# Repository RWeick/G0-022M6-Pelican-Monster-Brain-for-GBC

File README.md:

# G0-022M6-Pelican-Monster-Brain-for-GBC
The schematics, PCB, and flash dumps of three versions of the GBC Pelican Monster Brain.

Version 1.1 is for Pokemon Red and Blue, and comes in a case with a blue BrainBoy sticker/logo.
Version 2.0 is for Pokemon Gold and Silver, and comes in a case with a gold BrainBoy sticker/logo.
Version 3.6 is for every Gameboy Pokemon edition, and comes in a case with a purple Monster Brain sticker/logo.

All components labeled "Unknown" in the schematic were not present on the commercial PCB. This PCB is used for both the Monster Brain and the Codebreaker, and the missing components are present when this board is used in a Codebreaker.

The CPLD is the same between all devices.

The Colorizer button PCB wires solder to the inner two pads of the 4 at the rear top edge of the PCB.

Jumper configuration for normal operation: 

- J1: Pads 2 and 3 are shorted.
- J2: Open.
- J3: Shorted.
- J4: Shorted.

The CPLD functions I've been able to deduce are as follows:

A read must be performed at address 0x100 in order to enable address banking in the CPLD.

The write address to change banks is 0xA000.

The full rom is available from 0x2000 to 0x3FFF by switching either 32 or 64 banks depending on the device. The blue label Brainboy has 64 banks, and the rest of the devices use 32 banks due to smaller eeproms. The maximum known EEPROM size included with an off the shelf device is 512 KB.

PCB Thickness: 0.8 mm

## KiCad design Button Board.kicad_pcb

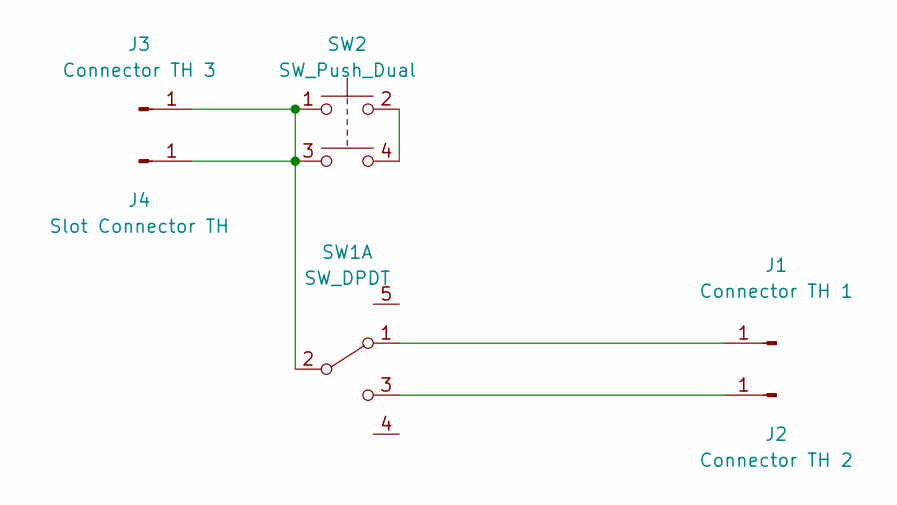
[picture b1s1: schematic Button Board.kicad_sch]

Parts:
J1: Connector TH 1; Connector Hole
J2: Connector TH 2; Connector Hole
J3: Connector TH 3; Connector Hole
J4: Slot Connector TH; Square Slot
SW1: SW_DPDT; Sliding Switch
SW2: SW_Push_Dual; Push Button

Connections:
unnamed: J1.1, SW1.1 (A)
unnamed: J2.1, SW1.3 (C)
unnamed: J3.1, J4.1, SW1.2 (B), SW2.1, SW2.3
unnamed: SW2.2, SW2.4

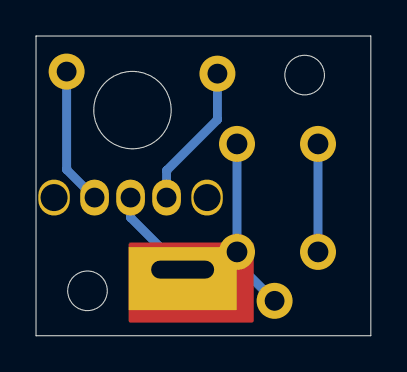
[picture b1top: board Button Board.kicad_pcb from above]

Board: 2 copper layers, 18.6 x 16.6 mm, 9 parts (0 on the bottom side), 4 nets.

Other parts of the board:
H1, H3: MountingHole_2.2mm_M2
H2: MountingHole_4.3mm_M4

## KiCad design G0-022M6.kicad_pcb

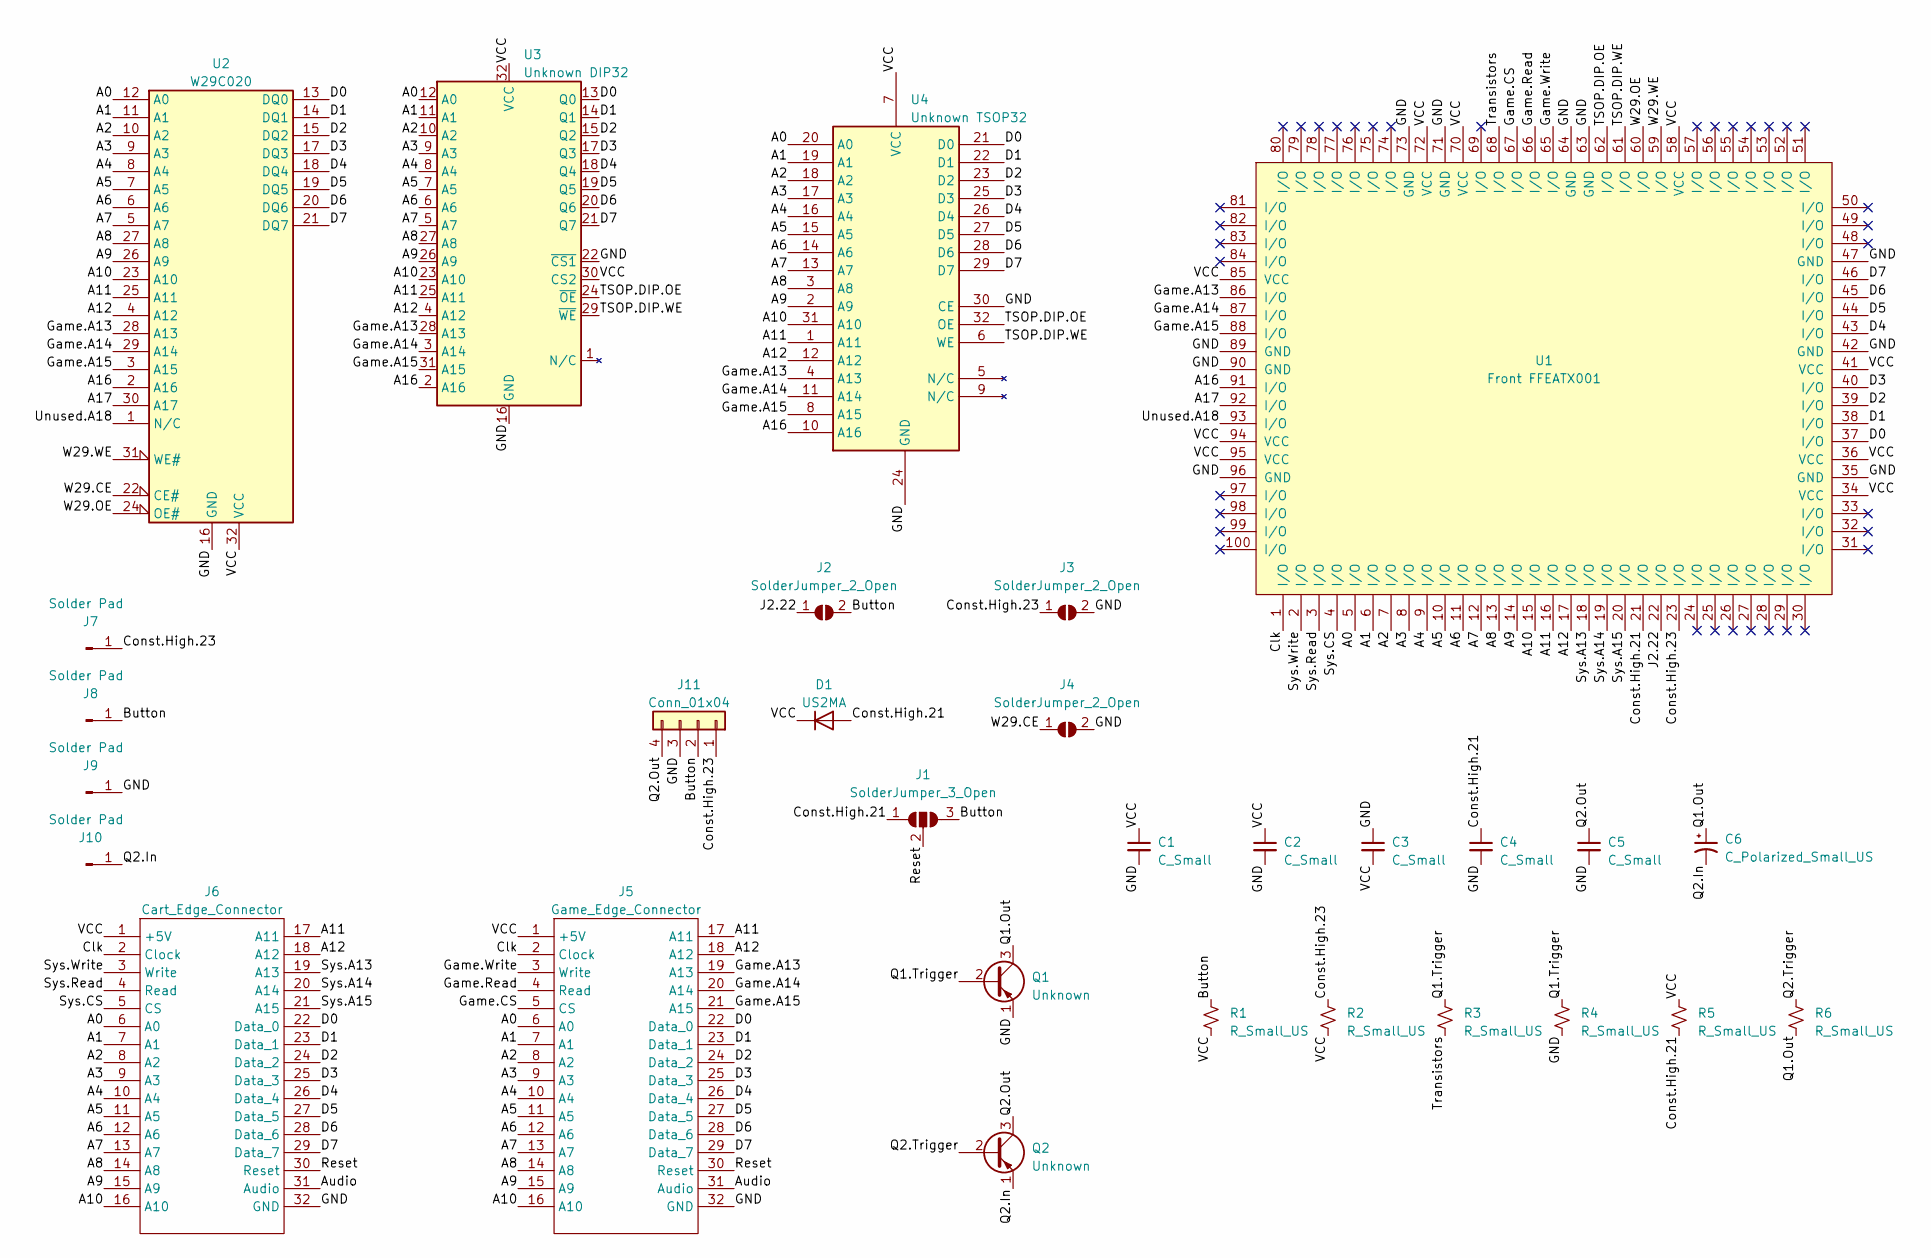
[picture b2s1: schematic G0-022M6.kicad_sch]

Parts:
C1, C2, C3, C4, C5: C_Small; SMD Cap
C6: C_Polarized_Small_US; TH Cap
D1: US2MA; Diode
J1: SolderJumper_3_Open; 3 Pad Jumper
J2, J3, J4: SolderJumper_2_Open; 2 Pad Jumper
J5: Game_Edge_Connector; Cartridge Slot, GBC
J6: Cart_Edge_Connector; ACTUAL GAMEBOY EDGE CONNECTOR
J7, J8, J9, J10: Solder Pad; Rear Circle Pad
J11: Conn_01x04; Rear Edge
Q1, Q2: Unknown; TO-92_Inline
R1, R2, R3, R4, R5, R6: R_Small_US; SMD Res
U1: Front FFEATX001; FFEATX001
U2: W29C020
U3: Unknown DIP32; Unknown Dip
U4: Unknown TSOP32; Unknown TSOP

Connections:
/A0: J5.6 (A0), J6.6 (A0), U1.5 (I/O), U2.12 (A0), U3.12 (A0), U4.20 (A0)
/A1: J5.7 (A1), J6.7 (A1), U1.6 (I/O), U2.11 (A1), U3.11 (A1), U4.19 (A1)
/A2: J5.8 (A2), J6.8 (A2), U1.7 (I/O), U2.10 (A2), U3.10 (A2), U4.18 (A2)
/A3: J5.9 (A3), J6.9 (A3), U1.8 (I/O), U2.9 (A3), U3.9 (A3), U4.17 (A3)
/A4: J5.10 (A4), J6.10 (A4), U1.9 (I/O), U2.8 (A4), U3.8 (A4), U4.16 (A4)
/A5: J5.11 (A5), J6.11 (A5), U1.10 (I/O), U2.7 (A5), U3.7 (A5), U4.15 (A5)
/A6: J5.12 (A6), J6.12 (A6), U1.11 (I/O), U2.6 (A6), U3.6 (A6), U4.14 (A6)
/A7: J5.13 (A7), J6.13 (A7), U1.12 (I/O), U2.5 (A7), U3.5 (A7), U4.13 (A7)
/A8: J5.14 (A8), J6.14 (A8), U1.13 (I/O), U2.27 (A8), U3.27 (A8), U4.3 (A8)
/A9: J5.15 (A9), J6.15 (A9), U1.14 (I/O), U2.26 (A9), U3.26 (A9), U4.2 (A9)
/A10: J5.16 (A10), J6.16 (A10), U1.15 (I/O), U2.23 (A10), U3.23 (A10), U4.31 (A10)
/A11: J5.17 (A11), J6.17 (A11), U1.16 (I/O), U2.25 (A11), U3.25 (A11), U4.1 (A11)
/A12: J5.18 (A12), J6.18 (A12), U1.17 (I/O), U2.4 (A12), U3.4 (A12), U4.12 (A12)
/A16: U1.91 (I/O), U2.2 (A16), U3.2 (A16), U4.10 (A16)
/A17: U1.92 (I/O), U2.30 (A17)
/Audio: J5.31 (Audio), J6.31 (Audio)
/Button: J1.3 (B), J2.2 (B), J8.1, J11.2, R1.1
/Clk: J5.2 (Clock), J6.2 (Clock), U1.1 (I/O)
/Const.High.21: C4.1, D1.2 (A), J1.1 (A), R5.2, U1.21 (I/O)
/Const.High.23: J3.1 (A), J7.1, J11.1, R2.1, U1.23 (I/O)
/D0: J5.22 (Data_0), J6.22 (Data_0), U1.37 (I/O), U2.13 (DQ0), U3.13 (Q0), U4.21 (D0)
/D1: J5.23 (Data_1), J6.23 (Data_1), U1.38 (I/O), U2.14 (DQ1), U3.14 (Q1), U4.22 (D1)
/D2: J5.24 (Data_2), J6.24 (Data_2), U1.39 (I/O), U2.15 (DQ2), U3.15 (Q2), U4.23 (D2)
/D3: J5.25 (Data_3), J6.25 (Data_3), U1.40 (I/O), U2.17 (DQ3), U3.17 (Q3), U4.25 (D3)
/D4: J5.26 (Data_4), J6.26 (Data_4), U1.43 (I/O), U2.18 (DQ4), U3.18 (Q4), U4.26 (D4)
/D5: J5.27 (Data_5), J6.27 (Data_5), U1.44 (I/O), U2.19 (DQ5), U3.19 (Q5), U4.27 (D5)
/D6: J5.28 (Data_6), J6.28 (Data_6), U1.45 (I/O), U2.20 (DQ6), U3.20 (Q6), U4.28 (D6)
/D7: J5.29 (Data_7), J6.29 (Data_7), U1.46 (I/O), U2.21 (DQ7), U3.21 (Q7), U4.29 (D7)
/GND: C1.2, C2.2, C3.1, C4.2, C5.2, J3.2 (B), J4.2 (B), J5.32 (GND), J6.32 (GND), J9.1, J11.3, Q1.1 (E), R4.2, U1.35 (GND), U1.42 (GND), U1.47 (GND), U1.63 (GND), U1.64 (GND), U1.71 (GND), U1.73 (GND), U1.89 (GND), U1.90 (GND), U1.96 (GND), U2.16 (GND), U3.16 (GND), U3.22 (~CS1), U4.24 (GND), U4.30 (CE)
/Game.A13: J5.19 (A13), U1.86 (I/O), U2.28 (A13), U3.28 (A13), U4.4 (A13)
/Game.A14: J5.20 (A14), U1.87 (I/O), U2.29 (A14), U3.3 (A14), U4.11 (A14)
/Game.A15: J5.21 (A15), U1.88 (I/O), U2.3 (A15), U3.31 (A15), U4.8 (A15)
/Game.CS: J5.5 (CS), U1.67 (I/O)
/Game.Read: J5.4 (Read), U1.66 (I/O)
/Game.Write: J5.3 (Write), U1.65 (I/O)
/J2.22: J2.1 (A), U1.22 (I/O)
/Q1.Out: C6.1, Q1.3 (C), R6.2
/Q1.Trigger: Q1.2 (B), R3.1, R4.1
/Q2.In: C6.2, J10.1, Q2.1 (E)
/Q2.Out: C5.1, J11.4, Q2.3 (C)
/Q2.Trigger: Q2.2 (B), R6.1
/Reset: J1.2 (C), J5.30 (Reset), J6.30 (Reset)
/Sys.A13: J6.19 (A13), U1.18 (I/O)
/Sys.A14: J6.20 (A14), U1.19 (I/O)
/Sys.A15: J6.21 (A15), U1.20 (I/O)
/Sys.CS: J6.5 (CS), U1.4 (I/O)
/Sys.Read: J6.4 (Read), U1.3 (I/O)
/Sys.Write: J6.3 (Write), U1.2 (I/O)
/TSOP.DIP.OE: U1.62 (I/O), U3.24 (~OE), U4.32 (OE)
/TSOP.DIP.WE: U1.61 (I/O), U3.29 (~WE), U4.6 (WE)
/Transistors: R3.2, U1.68 (I/O)
/Unused.A18: U1.93 (I/O), U2.1 (N/C)
/VCC: C1.1, C2.1, C3.2, D1.1 (K), J5.1 (+5V), J6.1 (+5V), R1.2, R2.2, R5.1, U1.34 (VCC), U1.36 (VCC), U1.41 (VCC), U1.58 (VCC), U1.70 (VCC), U1.72 (VCC), U1.85 (VCC), U1.94 (VCC), U1.95 (VCC), U2.32 (VCC), U3.30 (CS2), U3.32 (VCC), U4.7 (VCC)
/W29.CE: J4.1 (A), U2.22 (CE#)
/W29.OE: U1.60 (I/O), U2.24 (OE#)
/W29.WE: U1.59 (I/O), U2.31 (WE#)

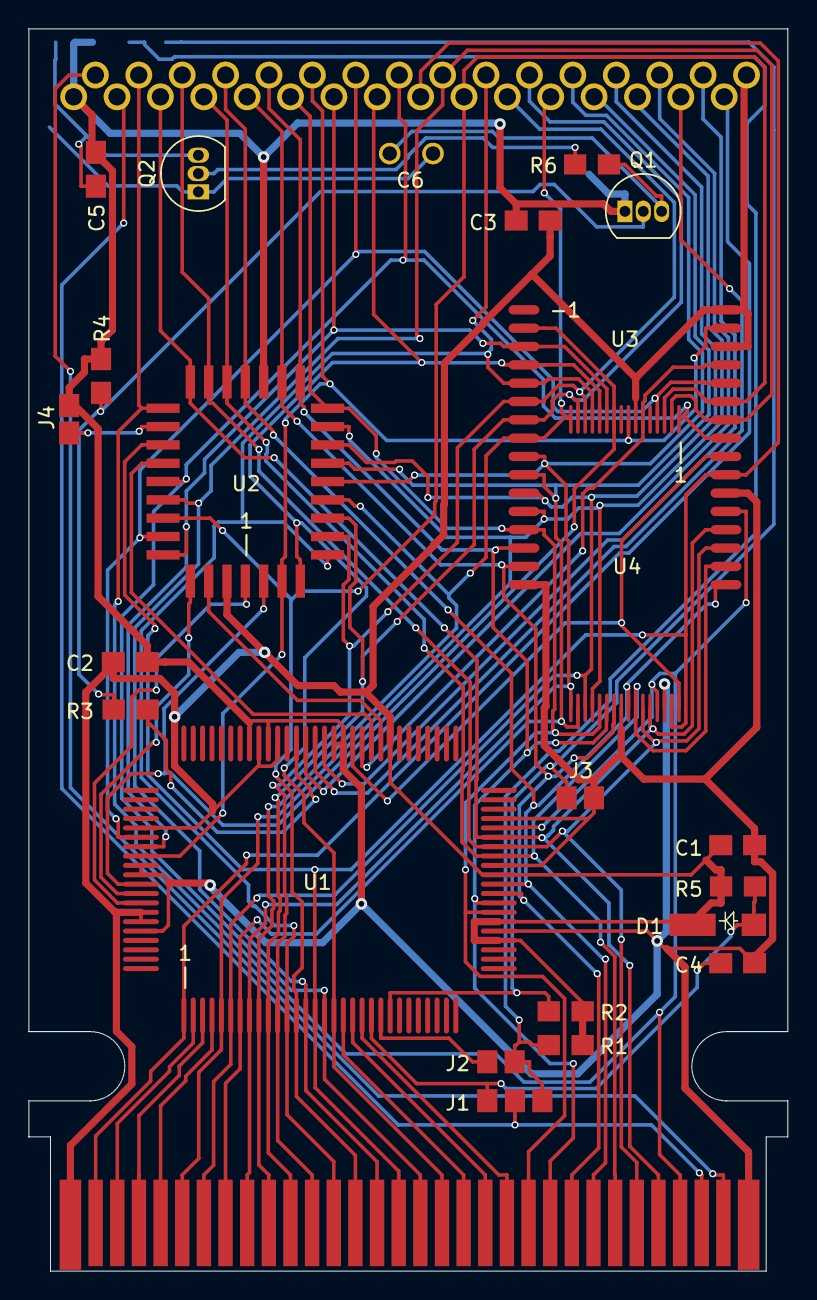
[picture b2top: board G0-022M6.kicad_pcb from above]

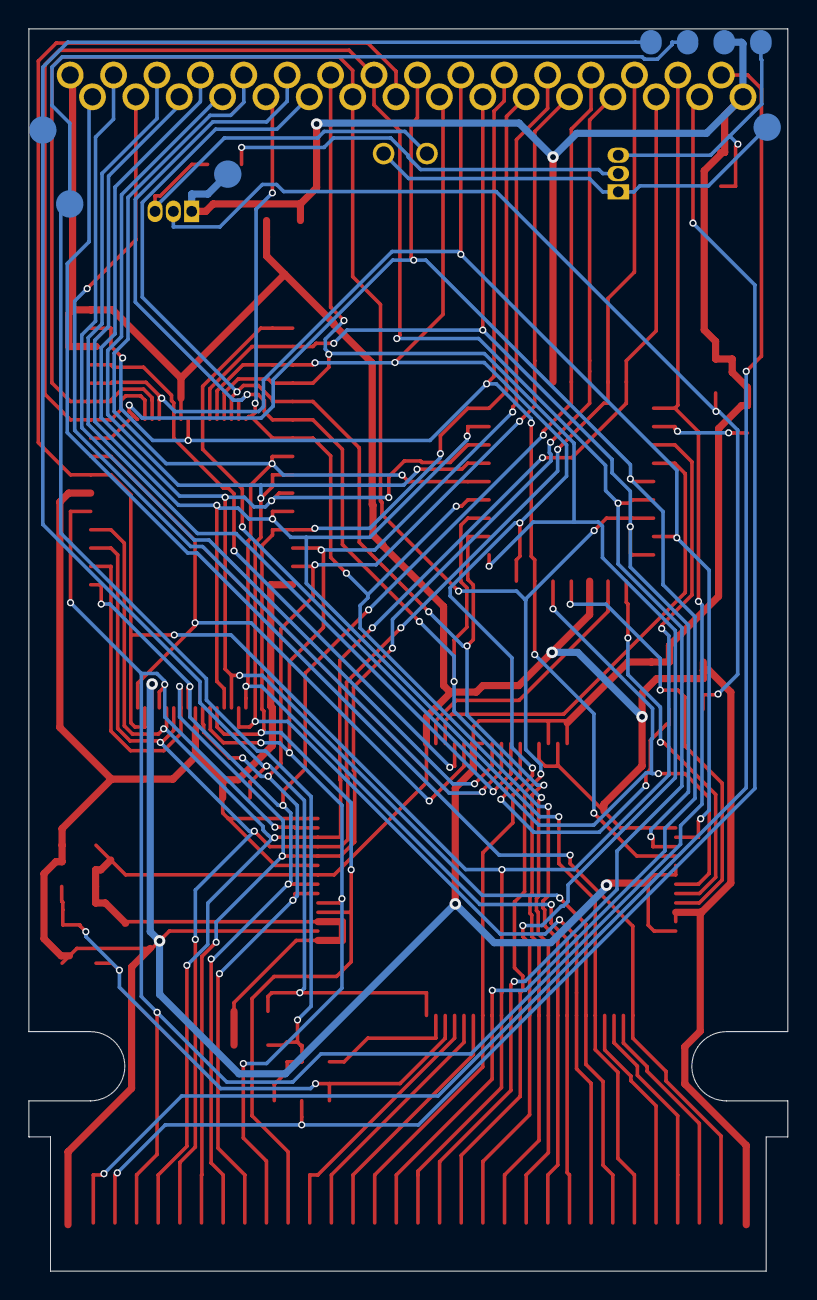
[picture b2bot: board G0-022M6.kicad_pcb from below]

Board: 2 copper layers, 52.6 x 86.1 mm, 30 parts (5 on the bottom side), 56 nets.
